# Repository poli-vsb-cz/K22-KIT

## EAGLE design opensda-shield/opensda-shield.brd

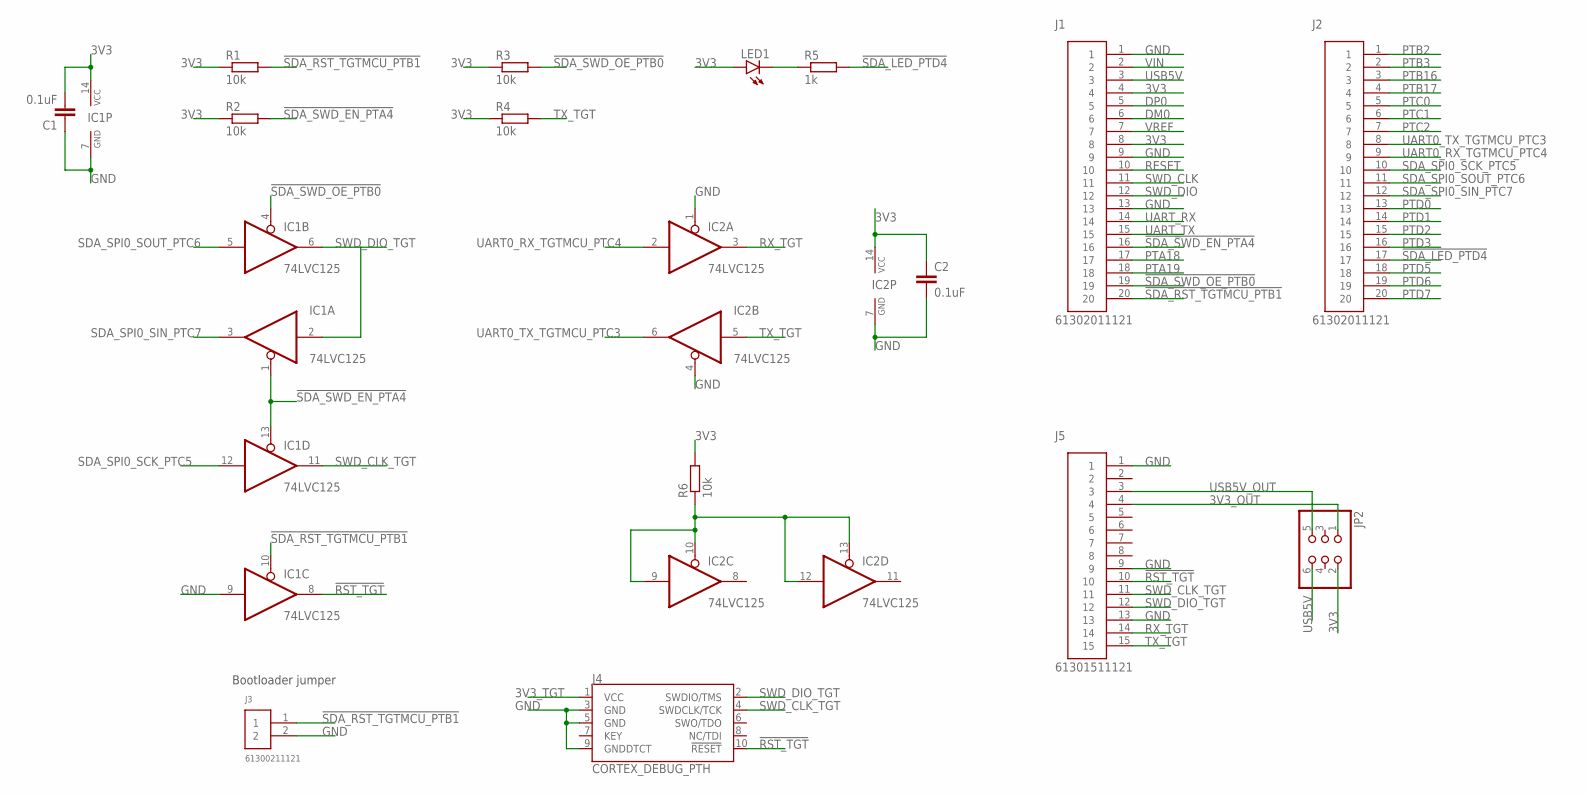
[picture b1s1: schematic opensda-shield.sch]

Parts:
C1, C2: 0.1uF; C0805
IC1, IC2: 74LVC125; TSSOP14
J1, J2: 61302011121
J3: 61300211121
J4: CORTEX_DEBUG_PTH; 2X5-PTH-1.27MM
J5: 61301511121
JP2: PINHD-2X3; 2X03
LED1: LEDCHIPLED_0805; CHIPLED_0805
R1, R2, R3, R4, R6: 10k; R0805
R5: 1k; R0805

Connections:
3V3: C1.2, C2.1, IC1.14 (VCC), IC2.14 (VCC), J1.4, J1.8, JP2.2, LED1.A, R1.1, R2.1, R3.1, R4.1, R6.2
3V3_OUT: J5.4, JP2.1
3V3_TGT: J4.1 (VCC)
!RST_TGT: IC1.8 (O), J4.10 (!RESET), J5.10
!SDA_LED_PTD4: J2.17, R5.2
!SDA_RST_TGTMCU_PTB1: IC1.10 (OE), J1.20, J3.1, R1.2
!SDA_SWD_EN_PTA4: IC1.1 (OE), IC1.13 (OE), J1.16, R2.2
!SDA_SWD_OE_PTB0: IC1.4 (OE), J1.19, R3.2
DM0: J1.6
DP0: J1.5
GND: C1.1, C2.2, IC1.7 (GND), IC1.9 (I), IC2.1 (OE), IC2.4 (OE), IC2.7 (GND), J1.1, J1.9, J1.13, J3.2, J4.3 (GND), J4.5 (GND), J4.9 (GNDDTCT), J5.1, J5.9, J5.13
unnamed: LED1.C, R5.1
unnamed: IC2.9 (I), IC2.10 (OE), IC2.12 (I), IC2.13 (OE), R6.1
PTA18: J1.17
PTA19: J1.18
PTB2: J2.1
PTB3: J2.2
PTB16: J2.3
PTB17: J2.4
PTC0: J2.5
PTC1: J2.6
PTC2: J2.7
PTD0: J2.13
PTD1: J2.14
PTD2: J2.15
PTD3: J2.16
PTD5: J2.18
PTD6: J2.19
PTD7: J2.20
RESET: J1.10
RX_TGT: IC2.3 (O), J5.14
SDA_SPI0_SCK_PTC5: IC1.12 (I), J2.10
SDA_SPI0_SIN_PTC7: IC1.3 (O), J2.12
SDA_SPI0_SOUT_PTC6: IC1.5 (I), J2.11
SWD_CLK: J1.11
SWD_CLK_TGT: IC1.11 (O), J4.4 (SWDCLK/TCK), J5.11
SWD_DIO: J1.12
SWD_DIO_TGT: IC1.2 (I), IC1.6 (O), J4.2 (SWDIO/TMS), J5.12
TX_TGT: IC2.5 (I), J5.15, R4.2
UART0_RX_TGTMCU_PTC4: IC2.2 (I), J2.9
UART0_TX_TGTMCU_PTC3: IC2.6 (O), J2.8
UART_RX: J1.14
UART_TX: J1.15
USB5V: J1.3, JP2.6
USB5V_OUT: J5.3, JP2.5
VIN: J1.2
VREF: J1.7

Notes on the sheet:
Bootloader jumper

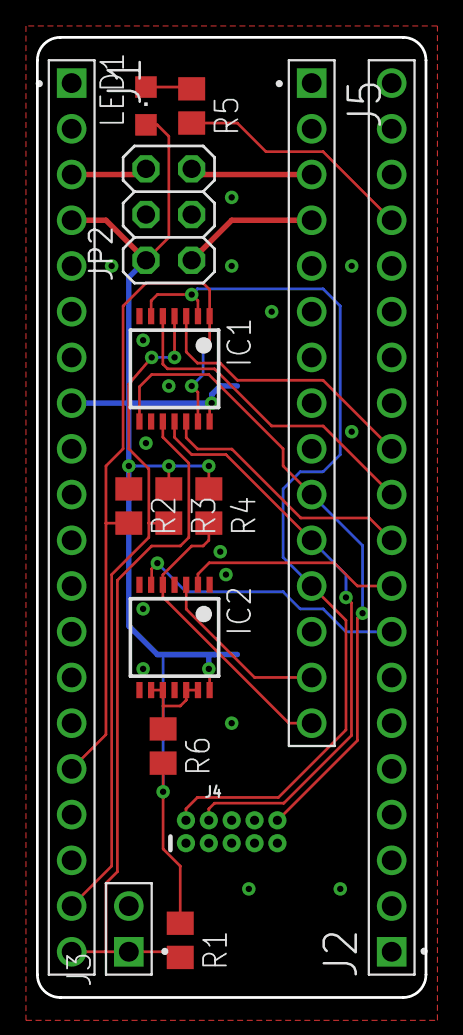
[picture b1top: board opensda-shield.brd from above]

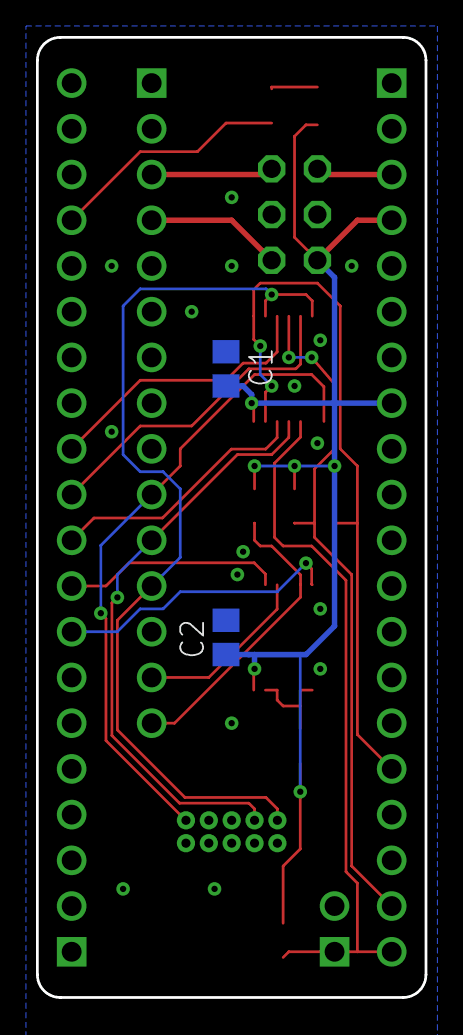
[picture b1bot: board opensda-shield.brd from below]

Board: 2 copper layers, 21.6 x 53.3 mm, 17 parts (2 on the bottom side), 21 nets.

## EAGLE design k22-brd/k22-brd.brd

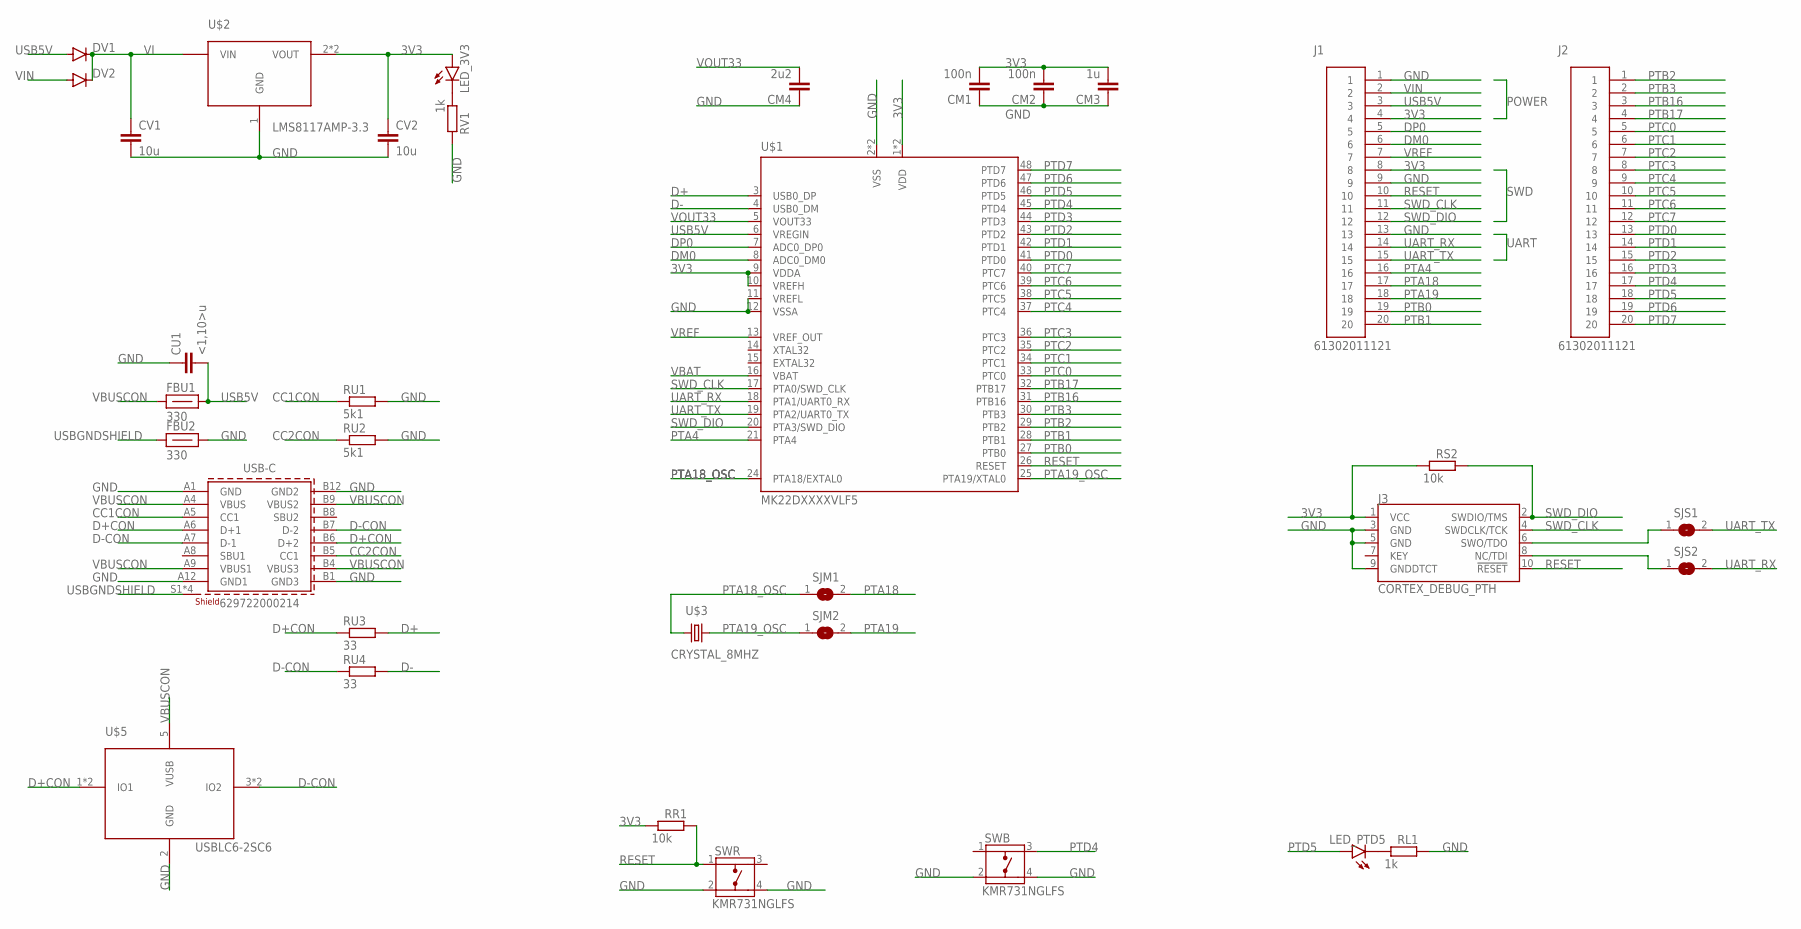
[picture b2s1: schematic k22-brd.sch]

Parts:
CM1, CM2: 100n; C0805
CM3: 1u; C0805
CM4: 2u2; C0805
CU1: <1,10>u; C0805
CV1, CV2: 10u; C0805
DV1, DV2: DIODE-DO214AC; DO214AC
FBU1, FBU2: 330; GHI-BASICCOMPONENTS_0805-RESISTOR
J1, J2: 61302011121
J3: CORTEX_DEBUG_PTH; 2X5-PTH-1.27MM
LED_3V3: LEDCHIP-LED0805; CHIP-LED0805
LED_PTD5: LEDCHIP-LED0805; CHIP-LED0805
RL1: 1k; M0805
RR1: 10k; M0805
RS2: 10k; M0805
RU1, RU2: 5k1; R0805
RU3, RU4: 33; R0805
RV1: 1k; M0805
SJM1, SJM2: SJ
SJS1, SJS2: SJ
SWB: KMR731NGLFS
SWR: KMR731NGLFS
U$1: MK22DXXXXVLF5; TQFP48_7X7
U$2: LMS8117AMP-3.3; SOT223
U$3: CRYSTAL_8MHZ; CRYSTAL-SMD-5X3.2-2PAD
U$5: USBLC6-2SC6; SOT23-6L
USB-C: 629722000214

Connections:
3V3: CM1.2, CM2.2, CM3.2, CV2.1, J1.4, J1.8, J3.1 (VCC), LED_3V3.A, RR1.1, RS2.1, U$1.1 (VDD), U$1.9 (VDDA), U$1.10 (VREFH), U$1.22 (VDD), U$2.2 (VOUT), U$2.4 (VOUT)
CC1CON: RU1.1, USB-C.A5 (CC1)
CC2CON: RU2.1, USB-C.B5 (CC1)
D+: RU3.2, U$1.3 (USB0_DP)
D+CON: RU3.1, U$5.1 (IO1), U$5.6 (IO1), USB-C.A6 (D+1), USB-C.B6 (D+2)
D-: RU4.2, U$1.4 (USB0_DM)
D-CON: RU4.1, U$5.3 (IO2), U$5.4 (IO2), USB-C.A7 (D-1), USB-C.B7 (D-2)
DM0: J1.6, U$1.8 (ADC0_DM0)
DP0: J1.5, U$1.7 (ADC0_DP0)
GND: CM1.1, CM2.1, CM3.1, CM4.1, CU1.1, CV1.2, CV2.2, FBU2.2, J1.1, J1.9, J1.13, J3.3 (GND), J3.5 (GND), J3.9 (GNDDTCT), RL1.2, RU1.2, RU2.2, RV1.2, SWB.2, SWB.4, SWR.2, SWR.4, U$1.2 (VSS), U$1.11 (VREFL), U$1.12 (VSSA), U$1.23 (VSS), U$2.1 (GND), U$5.2 (GND), USB-C.A1 (GND), USB-C.A12 (GND1), USB-C.B1 (GND3), USB-C.B12 (GND2)
unnamed: LED_PTD5.C, RL1.1
unnamed: LED_3V3.C, RV1.1
unnamed: J3.8 (NC/TDI), SJS2.1
unnamed: J3.6 (SWO/TDO), SJS1.1
PTA4: J1.16, U$1.21 (PTA4)
PTA18: J1.17, SJM1.2
PTA18_OSC: SJM1.1, U$1.24 (PTA18/EXTAL0), U$3.1
PTA19: J1.18, SJM2.2
PTA19_OSC: SJM2.1, U$1.25 (PTA19/XTAL0), U$3.2
PTB0: J1.19, U$1.27 (PTB0)
PTB1: J1.20, U$1.28 (PTB1)
PTB2: J2.1, U$1.29 (PTB2)
PTB3: J2.2, U$1.30 (PTB3)
PTB16: J2.3, U$1.31 (PTB16)
PTB17: J2.4, U$1.32 (PTB17)
PTC0: J2.5, U$1.33 (PTC0)
PTC1: J2.6, U$1.34 (PTC1)
PTC2: J2.7, U$1.35 (PTC2)
PTC3: J2.8, U$1.36 (PTC3)
PTC4: J2.9, U$1.37 (PTC4)
PTC5: J2.10, U$1.38 (PTC5)
PTC6: J2.11, U$1.39 (PTC6)
PTC7: J2.12, U$1.40 (PTC7)
PTD0: J2.13, U$1.41 (PTD0)
PTD1: J2.14, U$1.42 (PTD1)
PTD2: J2.15, U$1.43 (PTD2)
PTD3: J2.16, U$1.44 (PTD3)
PTD4: J2.17, SWB.3, U$1.45 (PTD4)
PTD5: J2.18, LED_PTD5.A, U$1.46 (PTD5)
PTD6: J2.19, U$1.47 (PTD6)
PTD7: J2.20, U$1.48 (PTD7)
RESET: J1.10, J3.10 (!RESET), RR1.2, SWR.1, U$1.26 (RESET)
SWD_CLK: J1.11, J3.4 (SWDCLK/TCK), U$1.17 (PTA0/SWD_CLK)
SWD_DIO: J1.12, J3.2 (SWDIO/TMS), RS2.2, U$1.20 (PTA3/SWD_DIO)
UART_RX: J1.14, SJS2.2, U$1.18 (PTA1/UART0_RX)
UART_TX: J1.15, SJS1.2, U$1.19 (PTA2/UART0_TX)
USB5V: CU1.2, DV1.A, FBU1.2, J1.3, U$1.6 (VREGIN)
USBGNDSHIELD: FBU2.1, USB-C.S1 (SHIELD), USB-C.S2 (SHIELD), USB-C.S3 (SHIELD), USB-C.S4 (SHIELD)
VBAT: U$1.16 (VBAT)
VBUSCON: FBU1.1, U$5.5 (VUSB), USB-C.A4 (VBUS), USB-C.A9 (VBUS1), USB-C.B4 (VBUS3), USB-C.B9 (VBUS2)
VI: CV1.1, DV1.C, DV2.C, U$2.3 (VIN)
VIN: DV2.A, J1.2
VOUT33: CM4.2, U$1.5 (VOUT33)
VREF: J1.7, U$1.13 (VREF_OUT)

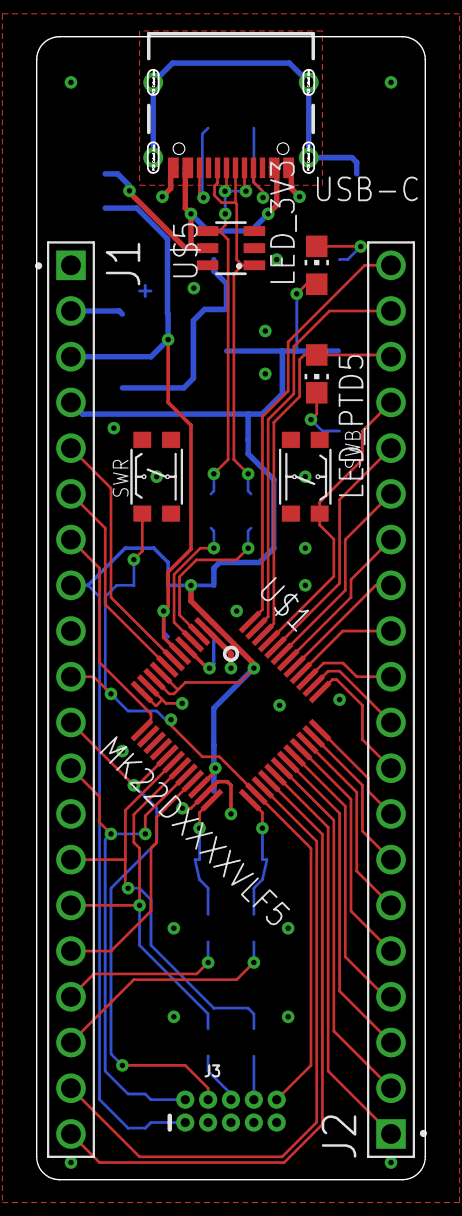
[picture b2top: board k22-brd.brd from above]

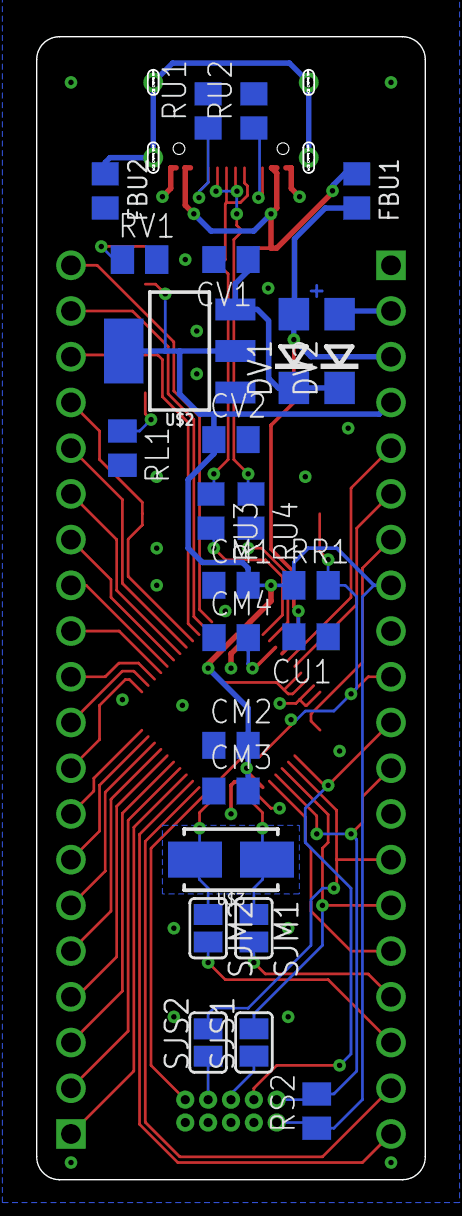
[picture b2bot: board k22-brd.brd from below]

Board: 2 copper layers, 21.6 x 63.5 mm, 35 parts (25 on the bottom side), 53 nets.

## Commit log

2022-07-03 init
2022-07-03 Added lib for ESD and Crystal and added those into brd schematic
2022-07-04 Renamed pin 5 on USBLC6
2022-07-04 schema is done
2022-07-04 board created
2022-07-07 Basic routing done
2022-07-07 Fixed routing
2022-07-08 Different pin order on headers
2022-07-08 Fixed DRC errors
2022-07-08 Improved routing
2022-07-08 Added gitignore
2022-07-08 prezehleno
2022-07-09 Nejake zmeny
2022-07-09 uprava routovani D+/-
2022-07-09 jen detaily
2022-07-09 Tlustsi cesticky
2022-07-09 Opraveno
2022-07-09 Opraveno 2
2022-07-09 10pin konektor blize k okraji a par drobnosti
2022-07-09 popis vrstva 111
2022-07-11 Pridane popisky
2022-07-11 Vetsi popisky - 0.9mm
2022-07-11 Pridan popis desky do textu
2022-07-11 do vyroby
2022-07-14 Pridany ramecky do schematu
2022-07-14 Modre ramecky
2022-07-14 Malinka uprava
2022-07-14 Vetsi text
2022-07-22 Pridany DESIGN_NOTES.md
2022-07-22 Upraveny DESIGN_NOTES.md
2022-08-04 Prejmenovan k22-shield na opensda-shield
2022-08-04 Prvni navrh opensda shieldu
2022-08-04 Pridana dalsi GND na 15pinovy konektor
2022-08-05 Zmeny podle e-mailu
2022-08-05 Zmena 74LVC125 package z SO14 na TSSOP14
2022-08-09 Prvni verze shieldu
2022-08-10 overlap, crystal pad, usb pad, bead pad
2022-08-10 Premisten J4 a prehozeny gaty bufferu
2022-08-10 Posunuti J4
2022-08-14 Pridany popisky
2022-08-14 Pridany znacky pinu 1
2022-08-14 Zapomenuty kulaty roh
2022-08-15 c1&c2&3v3->bot,text BSEL,vyzehleni
2022-08-15 layer 117->111
2022-08-16 Zmeny z e-mailu
2022-08-16 presun odporu
2022-08-17 Zmeny popisku
2022-09-01 Posunuti 10pin konektoru a zmena 2x2 jumperu na 3x2
2022-09-01 Male presuny
2022-09-04 OpenSDA shield v1.1
2022-09-04 Text v medi na spodni vrstve K22 desky
2022-09-04 Text z bKeepout do bStop
2022-09-07 oprava textu D4, dimension=3 mil
2022-09-07 drobne upravy
2022-09-07 Trochu zmeny textu
2022-09-11 v1.1 do vyroby

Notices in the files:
parts and their libraries:
SparkFun-Connectors: Licensing: Creative Commons ShareAlike 4.0 International - https://creativecommons.org/licenses/by-sa/4.0
